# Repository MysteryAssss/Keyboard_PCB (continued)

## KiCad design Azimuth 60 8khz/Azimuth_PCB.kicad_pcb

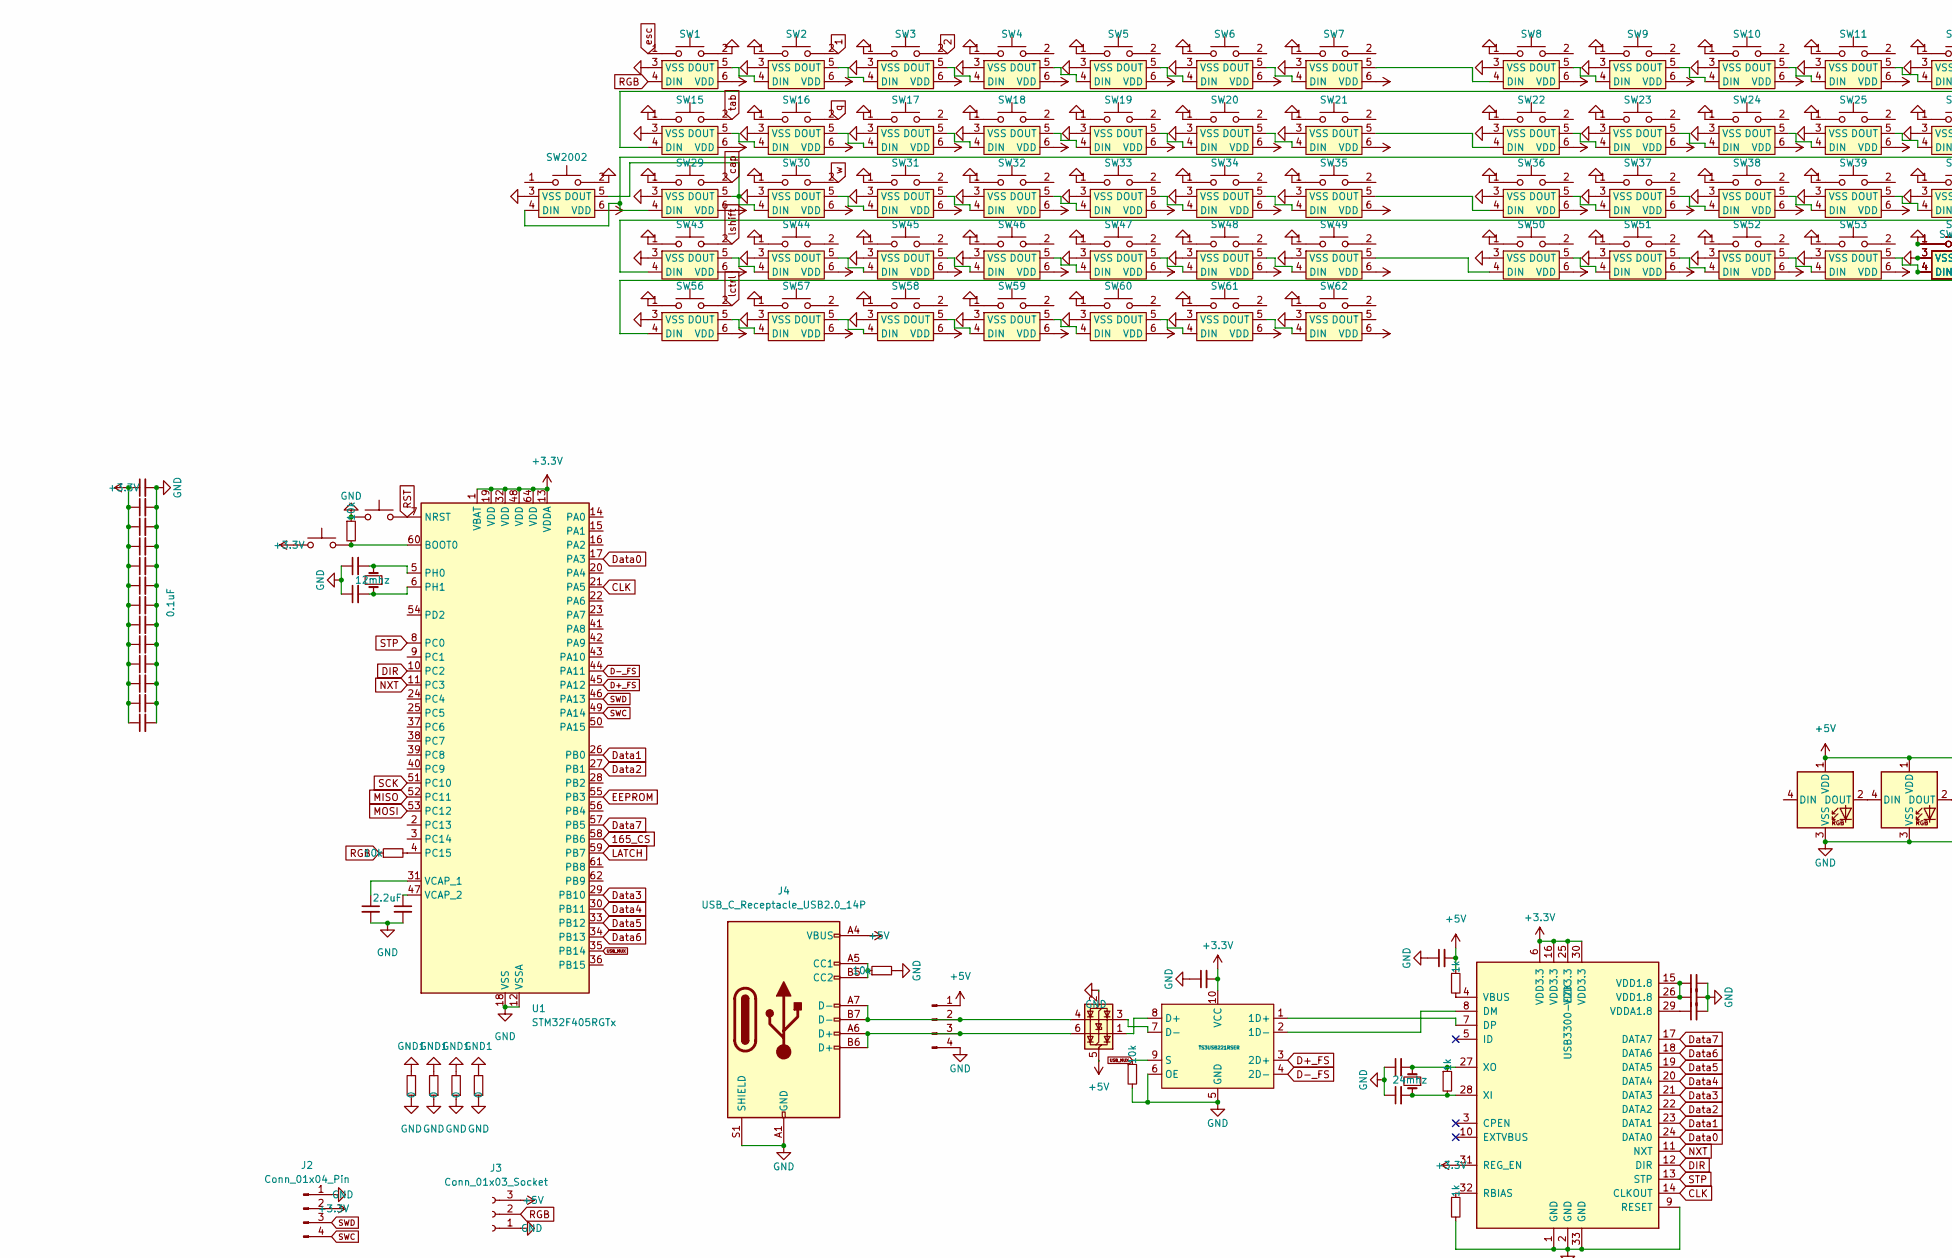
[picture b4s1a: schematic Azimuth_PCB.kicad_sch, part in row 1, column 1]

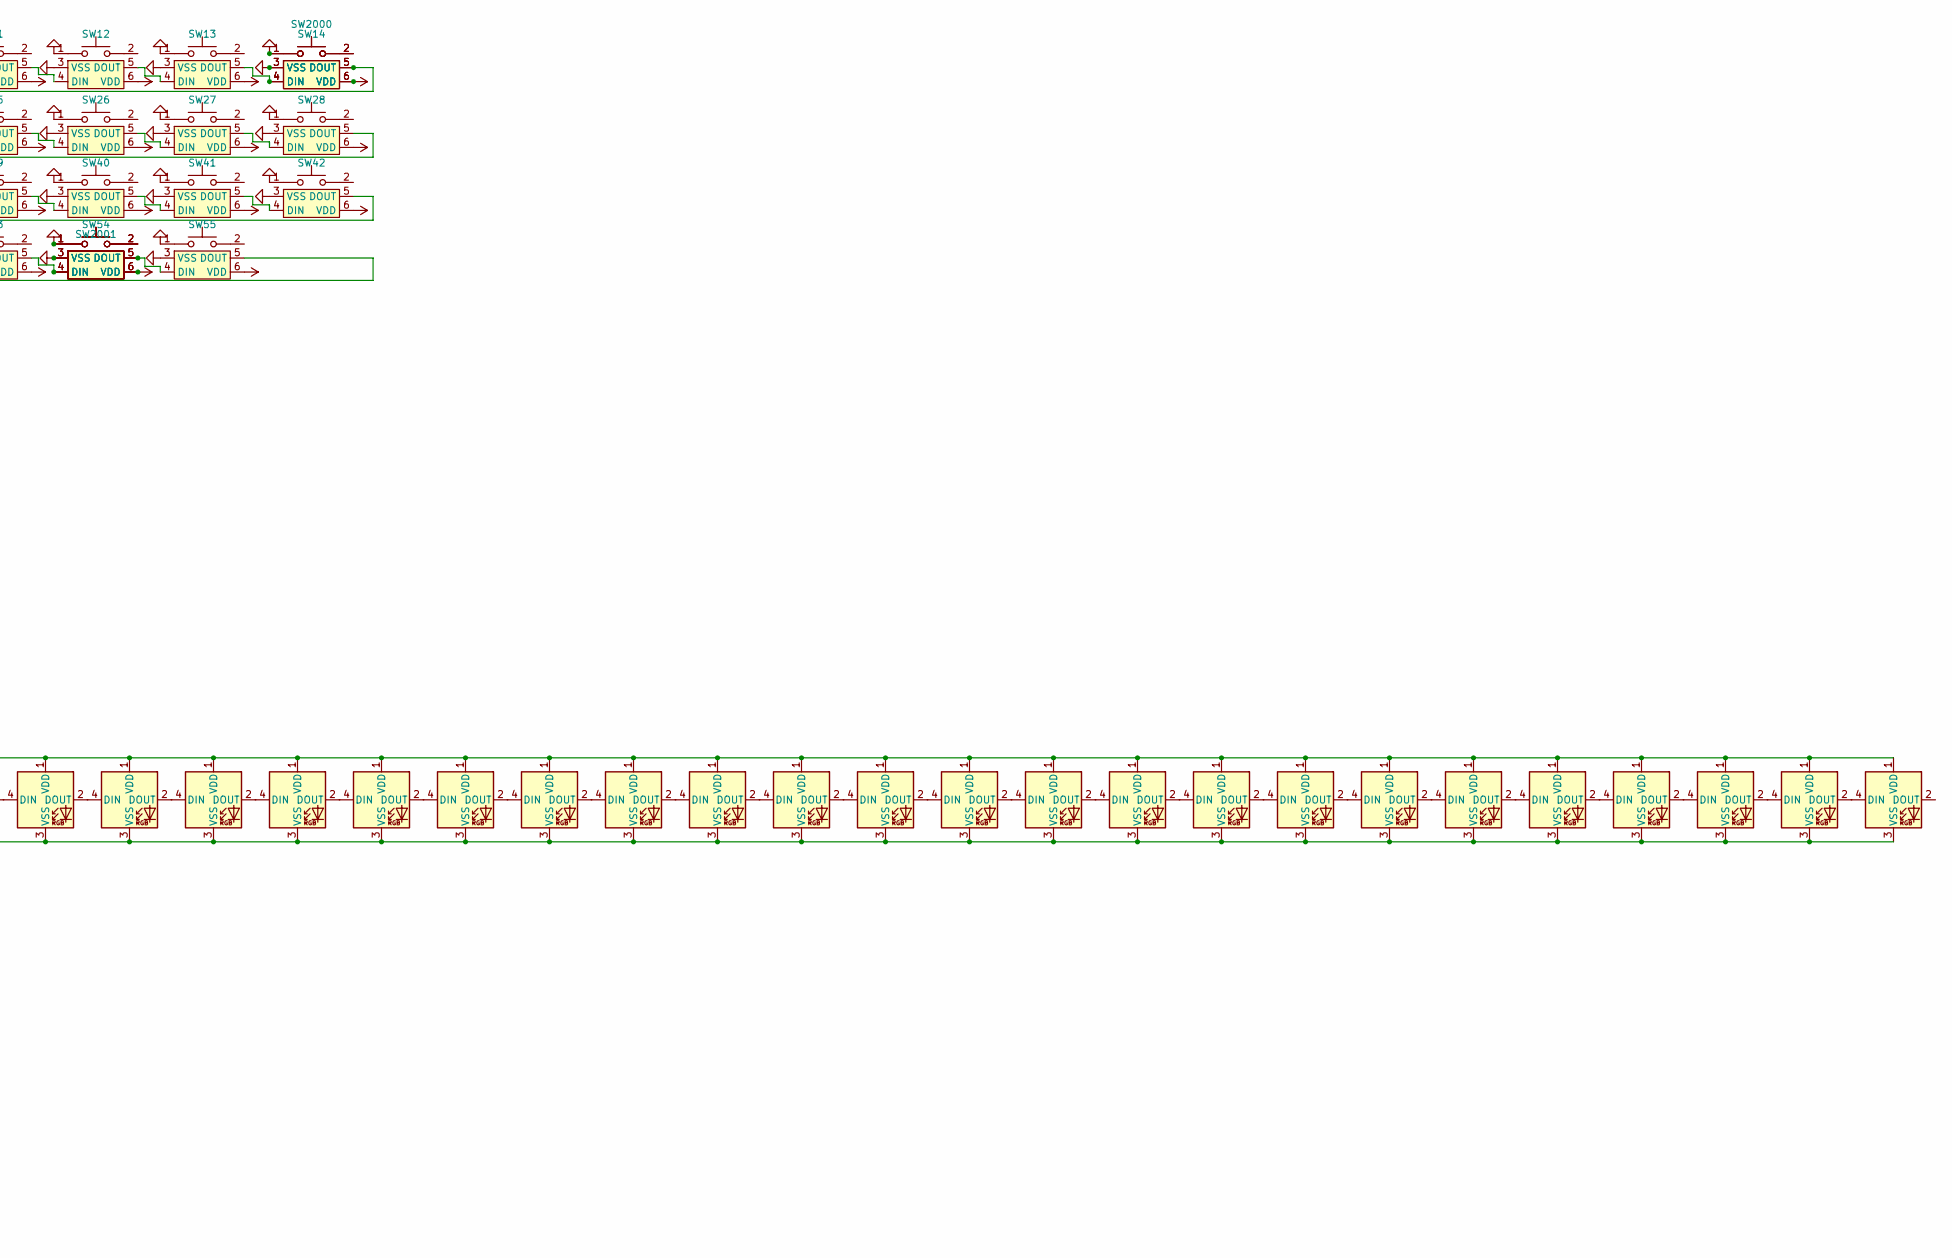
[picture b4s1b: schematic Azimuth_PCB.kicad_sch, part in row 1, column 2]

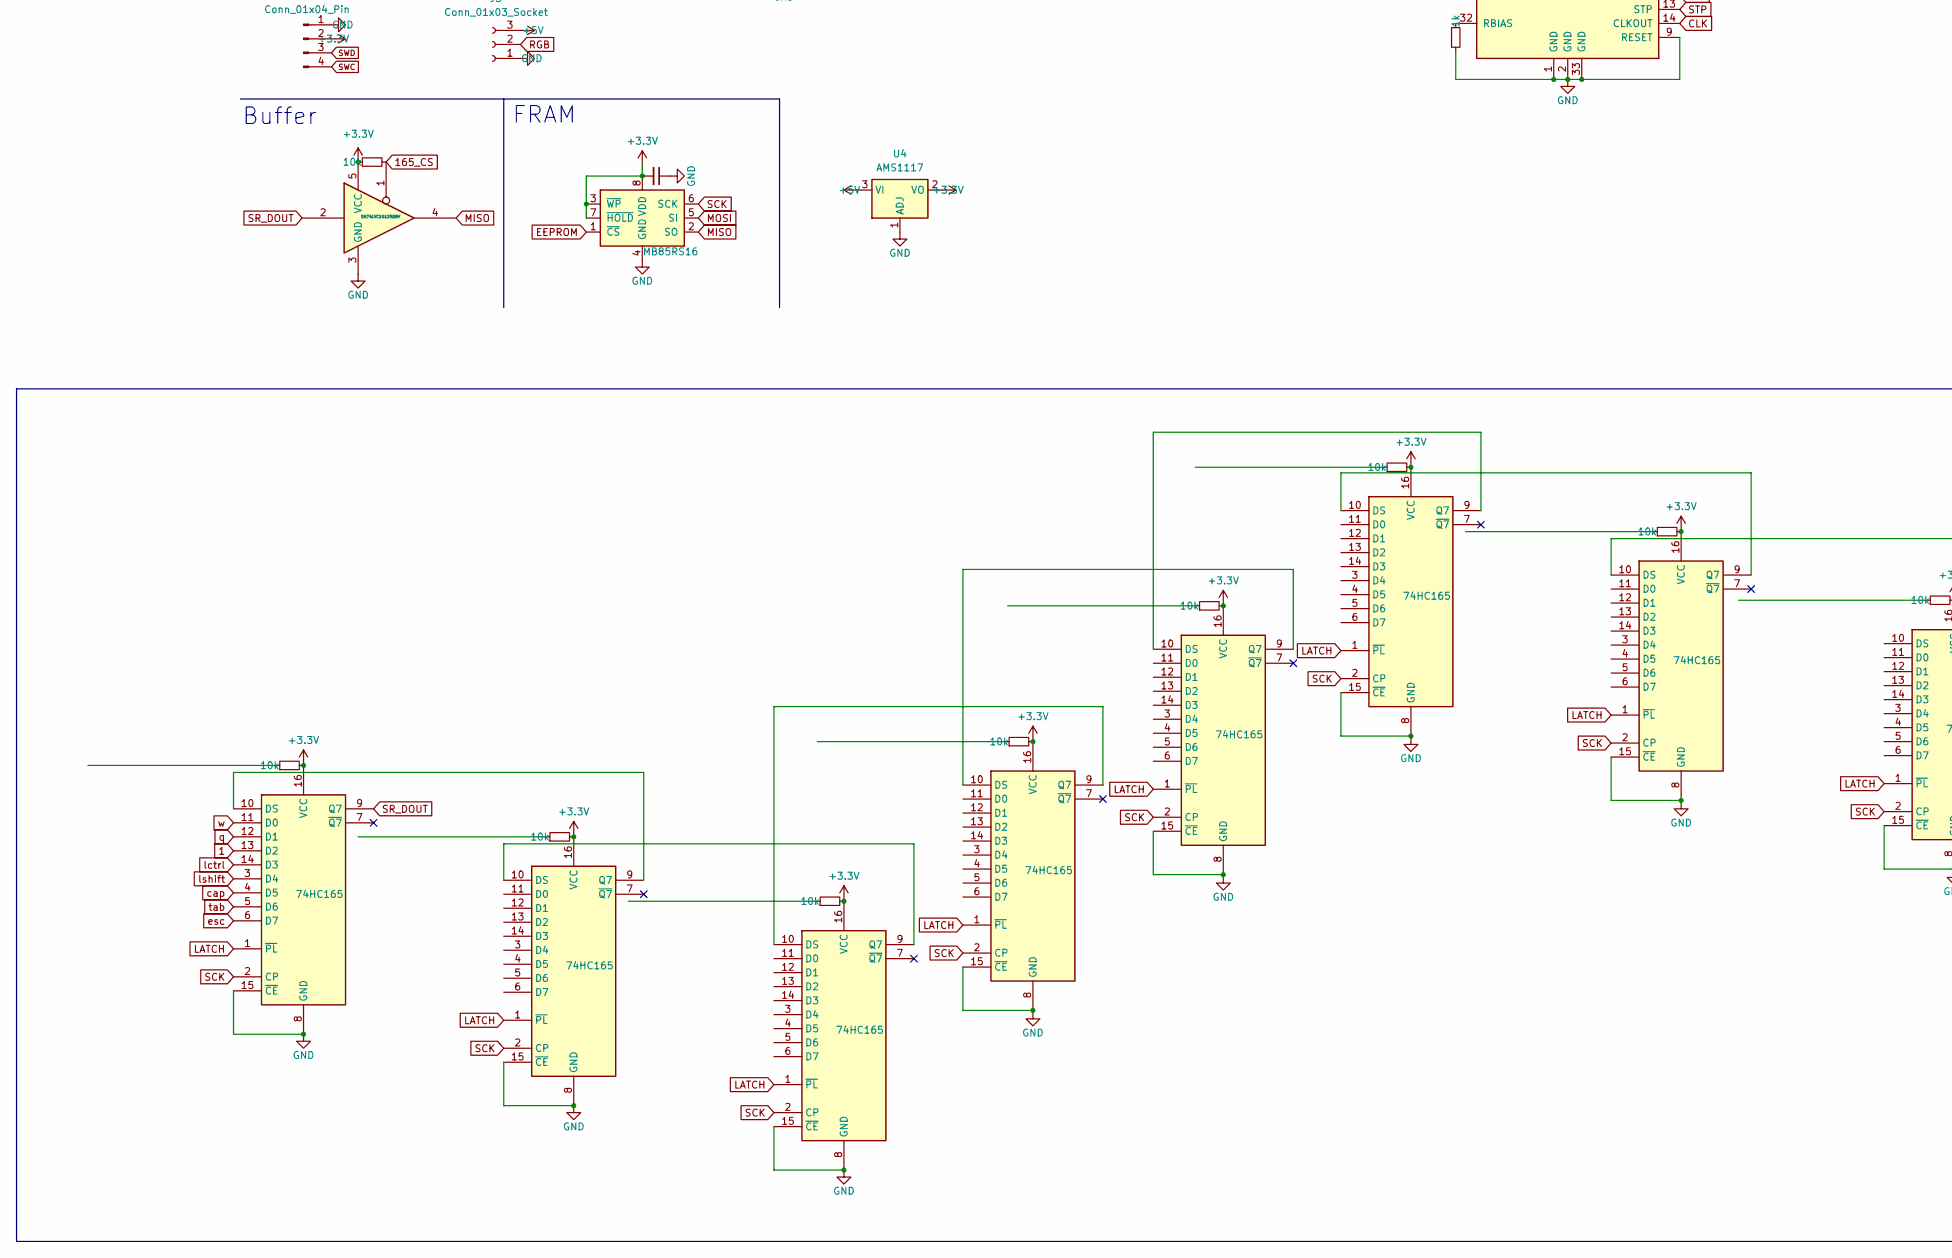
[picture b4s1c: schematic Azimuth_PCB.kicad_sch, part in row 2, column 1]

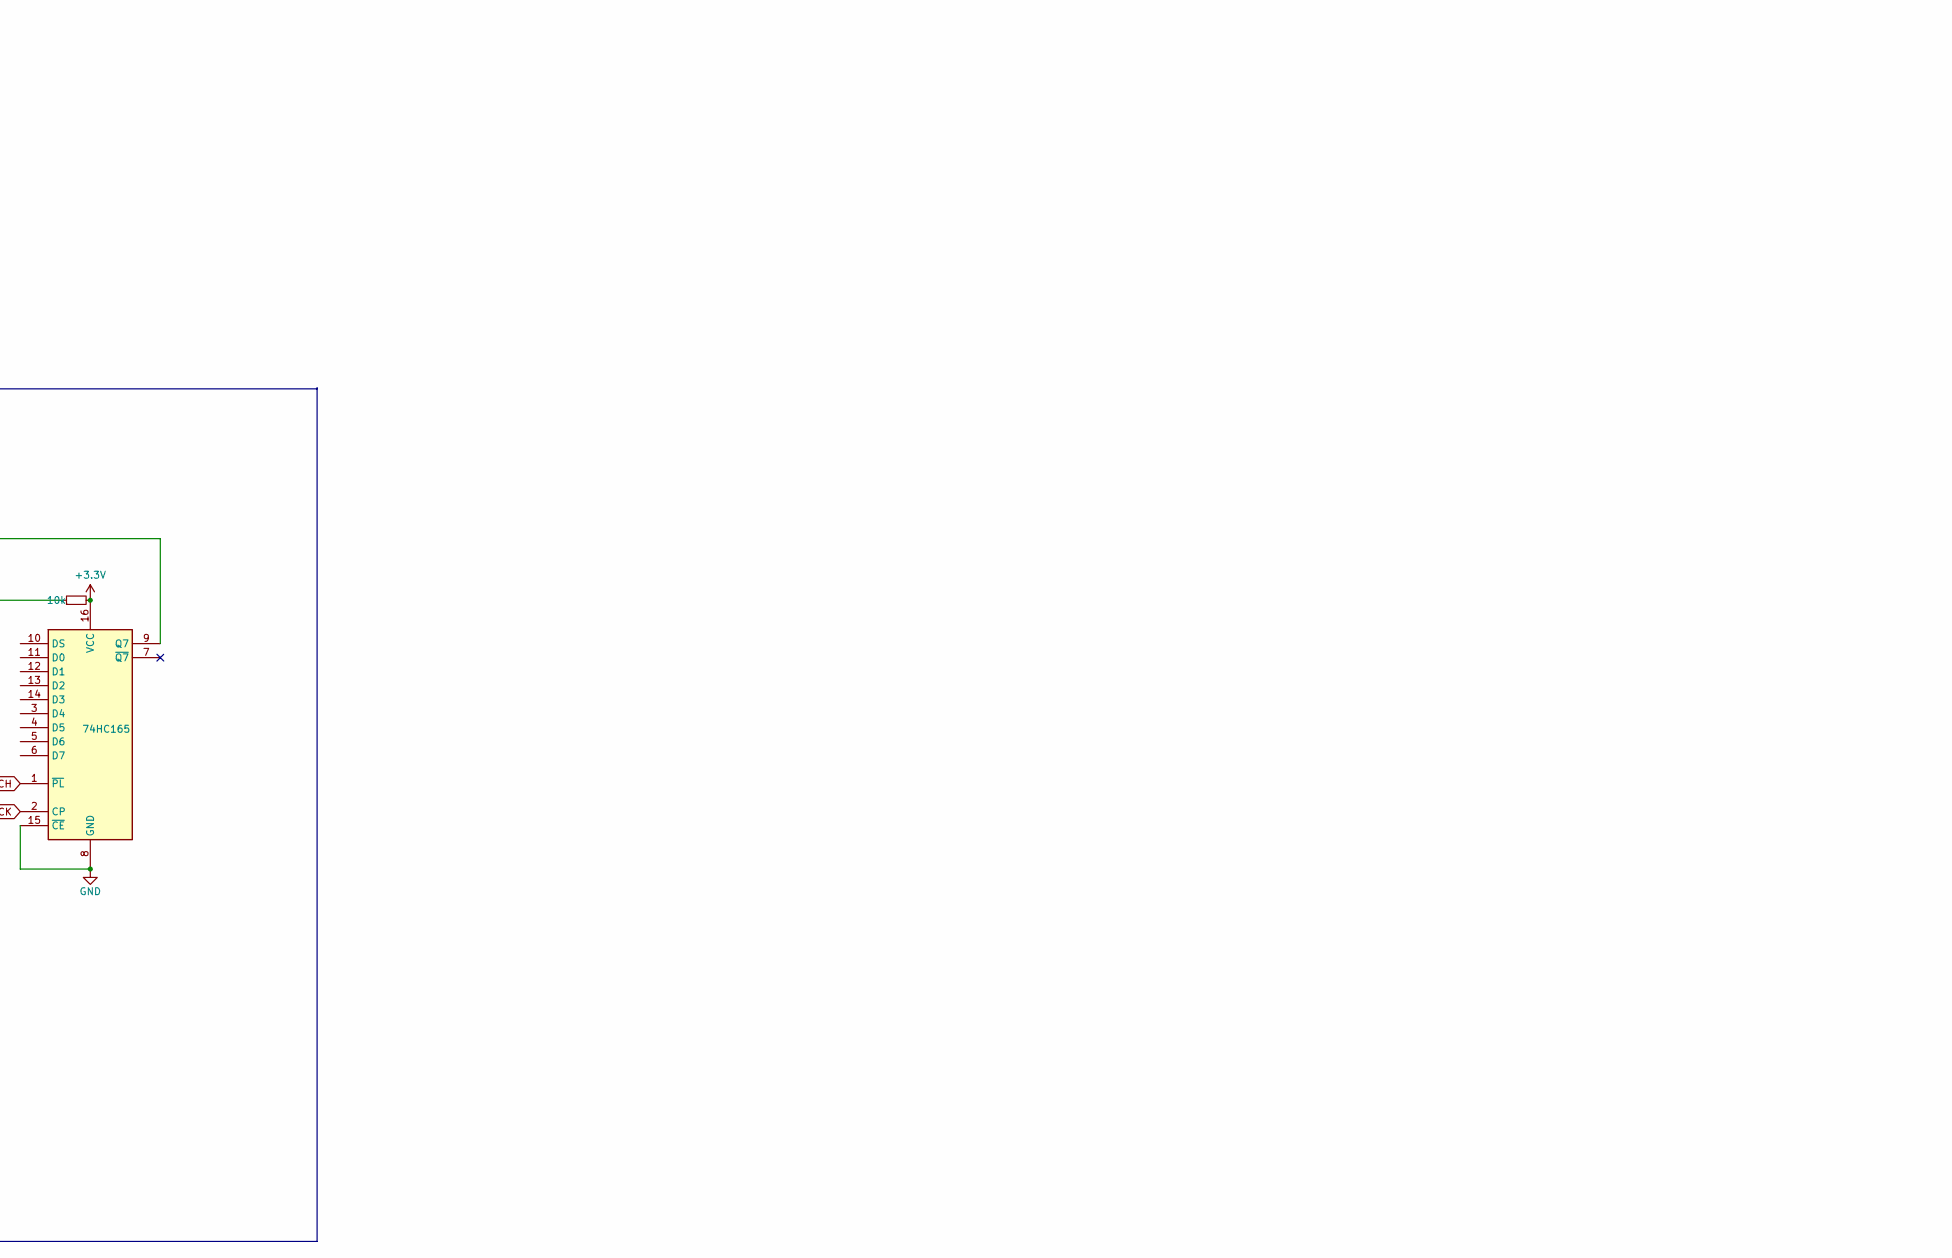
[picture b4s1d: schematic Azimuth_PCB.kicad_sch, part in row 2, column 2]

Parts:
C1, C2: 2.2uF; C_0603_1608Metric
C3, C4, C20, C21: 9pf; C_0603_1608Metric
C5, C6, C7, C8, C9, C10, C12, C14, C16: 0.1uF; C_0603_1608Metric
C11, C13, C15, C17, C18, C19, C22, C23, C24, C25: 1uF; C_0603_1608Metric
Drgb1, Drgb2, Drgb3, Drgb4, Drgb5, Drgb6, Drgb7, Drgb8, Drgb9, Drgb10, Drgb11, Drgb12, Drgb13, Drgb14, Drgb15, Drgb16, Drgb17, Drgb18, Drgb19, Drgb20, Drgb21, Drgb22, Drgb23, Drgb24: WS2812B; LED_WS2812B-2020_PLCC4_2.0x2.0mm
J1: Conn_01x04_Pin; JST_SH_SM04B-SRSS-TB_1x04-1MP_P1.00mm_Horizontal
J2: Conn_01x04_Pin; JST_EH_B4B-EH-A_1x04_P2.50mm_Vertical
J3: Conn_01x03_Socket; JST_SH_SM03B-SRSS-TB_1x03-1MP_P1.00mm_Horizontal
J4: USB_C_Receptacle_USB2.0_14P; USB_C_Receptacle_HRO_TYPE-C-31-M-12
R1, R2, R3, R4, R8, R9, R10, R11, R12, R13, R14, R15, R20: 10k; R_0603_1608Metric
R5, R6, R7: 1k; R_0603_1608Metric
R16, R17, R18, R19: 0; R_0603_1608Metric
SW1, SW2, SW3, SW4, SW5, SW6, SW7, SW8, SW9, SW10, SW11, SW12, SW13, SW14, SW16, SW17, SW18, SW19, SW20, SW21, SW22, SW23, SW24, SW25, SW26, SW27, SW30, SW31, SW32, SW33, SW34, SW35, SW36, SW37, SW38, SW39, SW40, SW42, SW44, SW45, SW46, SW47, SW48, SW49, SW50, SW51, SW52, SW53, SW55, SW57, SW61: CherryMX_LTST-A683CEGBW; MXOnly-1U_RGBs
SW15, SW28, SW56, SW58, SW60, SW62: CherryMX_LTST-A683CEGBW; MXOnly-1.5U_RGBs
SW29, SW54: CherryMX_LTST-A683CEGBW; MXOnly-1.75U_RGBs
SW41, SW43: CherryMX_LTST-A683CEGBW; MXOnly-2.25U_RGBs
SW59: CherryMX_LTST-A683CEGBW; MXOnly-7URGBs-ReversedStabilizers_N
SW2000: CherryMX_LTST-A683CEGBW; MXOnly-2U_RGBs
SW2001: CherryMX_LTST-A683CEGBW; MXOnly-2.75U_RGBs
SW2002: CherryMX_LTST-A683CEGBW; MXOnly-1.25U_RGBs
SWboot1, SWboot2: SW_Push; JST_XH_B2B-XH-A_1x02_P2.50mm_Vertical
U1: STM32F405RGTx; LQFP-64_10x10mm_P0.5mm
U2: SN74LVC1G125DBV; SOT-23-5
U3, U9, U10, U11, U12, U13, U14, U15: 74HC165; SOP-16_3.9x9.9mm_P1.27mm
U4: AMS1117; SOT-223-3_TabPin2
U5: TS3USB221RSER; UQFN-10
U6: USBLC6-2SC6; SOT-23-6
U7: USB3300-EZK; QFN-32-1EP_5x5mm_P0.5mm_EP3.45x3.45mm
U8: MB85RS16; SOIC-8_3.9x4.9mm_P1.27mm
Y1: 12mhz; Crystal_SMD_5032-2Pin_5.0x3.2mm
Y3: 24mhz; Crystal_SMD_5032-2Pin_5.0x3.2mm

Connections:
1: SW2.2, U3.13 (D2)
2: SW3.2
165_CS: R2.2, U1.58 (PB6), U2.1
+3.3V: C5.1, C6.1, C7.1, C8.1, C9.1, C10.1, C11.1, C12.1, C13.1, C14.1, C15.1, C16.1, C17.1, C18.2, C25.2, J2.2, R2.1, R3.2, R8.2, R9.2, R10.2, R11.2, R12.2, R13.2, R14.2, SWboot2.1, U1.1 (VBAT), U1.13 (VDDA), U1.19 (VDD), U1.32 (VDD), U1.48 (VDD), U1.64 (VDD), U2.5 (VCC), U3.16 (VCC), U4.2 (VO), U5.10 (VCC), U7.6 (VDD3.3), U7.16 (VDD3.3), U7.25 (VDD3.3), U7.30 (VDD3.3), U7.31 (REG_EN), U8.3 (~WP), U8.7 (~HOLD), U8.8 (VDD), U9.16 (VCC), U10.16 (VCC), U11.16 (VCC), U12.16 (VCC), U13.16 (VCC), U14.16 (VCC), U15.16 (VCC)
CLK: U1.21 (PA5), U7.14 (CLKOUT)
D+_FS: U1.45 (PA12), U5.3 (2D+)
D-_FS: U1.44 (PA11), U5.4 (2D-)
DIR: U1.10 (PC2), U7.12 (DIR)
Data0: U1.17 (PA3), U7.24 (DATA0)
Data1: U1.26 (PB0), U7.23 (DATA1)
Data2: U1.27 (PB1), U7.22 (DATA2)
Data3: U1.29 (PB10), U7.21 (DATA3)
Data4: U1.30 (PB11), U7.20 (DATA4)
Data5: U1.33 (PB12), U7.19 (DATA5)
Data6: U1.34 (PB13), U7.18 (DATA6)
Data7: U1.57 (PB5), U7.17 (DATA7)
EEPROM: U1.55 (PB3), U8.1 (~CS)
GND: C1.2, C2.2, C3.1, C4.1, C5.2, C6.2, C7.2, C8.2, C9.2, C10.2, C11.2, C12.2, C13.2, C14.2, C15.2, C16.2, C17.2, C18.1, C19.1, C20.1, C21.1, C22.2, C23.2, C24.2, C25.1, Drgb1.3 (VSS), Drgb2.3 (VSS), Drgb3.3 (VSS), Drgb4.3 (VSS), Drgb5.3 (VSS), Drgb6.3 (VSS), Drgb7.3 (VSS), Drgb8.3 (VSS), Drgb9.3 (VSS), Drgb10.3 (VSS), Drgb11.3 (VSS), Drgb12.3 (VSS), Drgb13.3 (VSS), Drgb14.3 (VSS), Drgb15.3 (VSS), Drgb16.3 (VSS), Drgb17.3 (VSS), Drgb18.3 (VSS), Drgb19.3 (VSS), Drgb20.3 (VSS), Drgb21.3 (VSS), Drgb22.3 (VSS), Drgb23.3 (VSS), Drgb24.3 (VSS), J1.4, J2.1, J3.1, J4.A1 (GND), J4.A12 (GND), J4.B1 (GND), J4.B12 (GND), J4.S1 (SHIELD), R1.1, R4.2, R7.2, R16.1, R17.1, R18.1, R19.1, R20.2, SW1.3 (VSS), SW2.3 (VSS), SW3.3 (VSS), SW4.3 (VSS), SW5.3 (VSS), SW6.3 (VSS), SW7.3 (VSS), SW8.3 (VSS), SW9.3 (VSS), SW10.3 (VSS), SW11.3 (VSS), SW12.3 (VSS), SW13.3 (VSS), SW14.3 (VSS), SW15.3 (VSS), SW16.3 (VSS), SW17.3 (VSS), SW18.3 (VSS), SW19.3 (VSS), SW20.3 (VSS), SW21.3 (VSS), SW22.3 (VSS), SW23.3 (VSS), SW24.3 (VSS), SW25.3 (VSS), SW26.3 (VSS), SW27.3 (VSS), SW28.3 (VSS), SW29.3 (VSS), SW30.3 (VSS), SW31.3 (VSS), SW32.3 (VSS), SW33.3 (VSS), SW34.3 (VSS), SW35.3 (VSS), SW36.3 (VSS), SW37.3 (VSS), SW38.3 (VSS), SW39.3 (VSS), SW40.3 (VSS), SW41.3 (VSS), SW42.3 (VSS), SW43.3 (VSS), SW44.3 (VSS), SW45.3 (VSS), SW46.3 (VSS), SW47.3 (VSS), SW48.3 (VSS), SW49.3 (VSS), SW50.3 (VSS), SW51.3 (VSS), SW52.3 (VSS), SW53.3 (VSS), SW54.3 (VSS), SW55.3 (VSS), SW56.3 (VSS), SW57.3 (VSS), SW58.3 (VSS), SW59.3 (VSS), SW60.3 (VSS), SW61.3 (VSS), SW62.3 (VSS), SW2000.3 (VSS), SW2001.3 (VSS), SW2002.3 (VSS), SWboot1.1, U1.12 (VSSA), U1.18 (VSS), U1.63 (VSS), U2.3 (GND), U3.8 (GND), U3.15 (~CE), U4.1 (ADJ), U5.5 (GND), U5.6 (OE), U6.2 (GND), U7.1 (GND), U7.2 (GND), U7.9 (RESET), U7.33 (GND), U8.4 (GND), U9.8 (GND), U9.15 (~CE), U10.8 (GND), U10.15 (~CE), U11.8 (GND), U11.15 (~CE), U12.8 (GND), U12.15 (~CE), U13.8 (GND), U13.15 (~CE), U14.8 (GND), U14.15 (~CE), U15.8 (GND), U15.15 (~CE)
GND1: R16.2, R17.2, R18.2, R19.2, SW1.2, SW2.1, SW3.1, SW4.1, SW5.1, SW6.1, SW7.1, SW8.1, SW9.1, SW10.1, SW11.1, SW12.1, SW13.1, SW14.1, SW15.1, SW16.1, SW17.1, SW18.1, SW19.1, SW20.1, SW21.1, SW22.1, SW23.1, SW24.1, SW25.1, SW26.1, SW27.1, SW28.1, SW29.1, SW30.1, SW31.1, SW32.1, SW33.1, SW34.1, SW35.1, SW36.1, SW37.1, SW38.1, SW39.1, SW40.1, SW41.1, SW42.1, SW43.1, SW44.1, SW45.1, SW46.1, SW47.1, SW48.1, SW49.1, SW50.1, SW51.1, SW52.1, SW53.1, SW54.1, SW55.1, SW56.1, SW57.1, SW58.1, SW59.1, SW60.1, SW61.1, SW62.1, SW2000.1, SW2001.1, SW2002.2
LATCH: U1.59 (PB7), U3.1 (~PL), U9.1 (~PL), U10.1 (~PL), U11.1 (~PL), U12.1 (~PL), U13.1 (~PL), U14.1 (~PL), U15.1 (~PL)
MISO: U1.52 (PC11), U2.4, U8.2 (SO)
MOSI: U1.53 (PC12), U8.5 (SI)
NXT: U1.11 (PC3), U7.11 (NXT)
unnamed: C22.1, C23.1, U7.15 (VDD1.8), U7.26 (VDD1.8)
unnamed: Drgb1.4 (DIN), Drgb16.2 (DOUT)
unnamed: Drgb1.2 (DOUT), Drgb2.4 (DIN)
unnamed: Drgb2.2 (DOUT), Drgb3.4 (DIN)
unnamed: Drgb3.2 (DOUT), Drgb4.4 (DIN)
unnamed: Drgb4.2 (DOUT), Drgb5.4 (DIN)
unnamed: Drgb5.2 (DOUT), Drgb6.4 (DIN)
unnamed: Drgb6.2 (DOUT), Drgb7.4 (DIN)
unnamed: Drgb7.2 (DOUT), Drgb8.4 (DIN)
unnamed: Drgb8.2 (DOUT), Drgb9.4 (DIN)
unnamed: Drgb9.2 (DOUT), Drgb10.4 (DIN)
unnamed: Drgb10.2 (DOUT), Drgb11.4 (DIN)
unnamed: Drgb11.2 (DOUT), Drgb12.4 (DIN)
unnamed: Drgb12.2 (DOUT), Drgb13.4 (DIN)
unnamed: Drgb13.2 (DOUT), Drgb14.4 (DIN)
unnamed: Drgb14.2 (DOUT), Drgb15.4 (DIN)
unnamed: Drgb15.2 (DOUT), Drgb17.4 (DIN)
unnamed: Drgb17.2 (DOUT), Drgb18.4 (DIN)
unnamed: Drgb18.2 (DOUT), Drgb19.4 (DIN)
unnamed: Drgb19.2 (DOUT), Drgb20.4 (DIN)
unnamed: Drgb20.2 (DOUT), Drgb21.4 (DIN)
unnamed: Drgb21.2 (DOUT), Drgb22.4 (DIN)
unnamed: Drgb22.2 (DOUT), Drgb23.4 (DIN)
unnamed: Drgb23.2 (DOUT), Drgb24.4 (DIN)
unnamed: J1.2, J4.A7 (D-), J4.B7 (D-), U6.4 (I/O2)
unnamed: J1.3, J4.A6 (D+), J4.B6 (D+), U6.6 (I/O1)
unnamed: J4.A5 (CC1), J4.B5 (CC2), R20.1
unnamed: SW1.5 (DOUT), SW2.4 (DIN)
unnamed: SW2.5 (DOUT), SW3.4 (DIN)
unnamed: SW3.5 (DOUT), SW4.4 (DIN)
unnamed: SW4.5 (DOUT), SW5.4 (DIN)
unnamed: SW5.5 (DOUT), SW6.4 (DIN)
unnamed: SW6.5 (DOUT), SW7.4 (DIN)
unnamed: SW7.5 (DOUT), SW8.4 (DIN)
unnamed: SW8.5 (DOUT), SW9.4 (DIN)
unnamed: SW9.5 (DOUT), SW10.4 (DIN)
unnamed: SW10.5 (DOUT), SW11.4 (DIN)
unnamed: SW11.5 (DOUT), SW12.4 (DIN)
unnamed: SW12.5 (DOUT), SW13.4 (DIN)
unnamed: SW13.5 (DOUT), SW14.4 (DIN), SW2000.4 (DIN)
unnamed: SW14.5 (DOUT), SW15.4 (DIN), SW2000.5 (DOUT)
unnamed: SW14.2, SW2000.2
unnamed: SW15.5 (DOUT), SW16.4 (DIN)
unnamed: SW16.5 (DOUT), SW17.4 (DIN)
unnamed: SW17.5 (DOUT), SW18.4 (DIN)
unnamed: SW18.5 (DOUT), SW19.4 (DIN)
unnamed: SW19.5 (DOUT), SW20.4 (DIN)
unnamed: SW20.5 (DOUT), SW21.4 (DIN)
unnamed: SW21.5 (DOUT), SW22.4 (DIN)
unnamed: SW22.5 (DOUT), SW23.4 (DIN)
unnamed: SW23.5 (DOUT), SW24.4 (DIN)
unnamed: SW24.5 (DOUT), SW25.4 (DIN)
unnamed: SW25.5 (DOUT), SW26.4 (DIN)
unnamed: SW26.5 (DOUT), SW27.4 (DIN)
unnamed: SW27.5 (DOUT), SW28.4 (DIN)
unnamed: SW30.5 (DOUT), SW31.4 (DIN)
unnamed: SW31.5 (DOUT), SW32.4 (DIN)
unnamed: SW32.5 (DOUT), SW33.4 (DIN)
unnamed: SW33.5 (DOUT), SW34.4 (DIN)
unnamed: SW34.5 (DOUT), SW35.4 (DIN)
unnamed: SW35.5 (DOUT), SW36.4 (DIN)
unnamed: SW36.5 (DOUT), SW37.4 (DIN)
unnamed: SW37.5 (DOUT), SW38.4 (DIN)
unnamed: SW38.5 (DOUT), SW39.4 (DIN)
unnamed: SW39.5 (DOUT), SW40.4 (DIN)
unnamed: SW40.5 (DOUT), SW41.4 (DIN)
unnamed: SW41.5 (DOUT), SW42.4 (DIN)
unnamed: SW42.5 (DOUT), SW43.4 (DIN)
unnamed: SW43.5 (DOUT), SW44.4 (DIN)
unnamed: SW44.5 (DOUT), SW45.4 (DIN)
unnamed: SW45.5 (DOUT), SW46.4 (DIN)
unnamed: SW46.5 (DOUT), SW47.4 (DIN)
unnamed: SW47.5 (DOUT), SW48.4 (DIN)
unnamed: SW48.5 (DOUT), SW49.4 (DIN)
unnamed: SW49.5 (DOUT), SW50.4 (DIN)
unnamed: SW50.5 (DOUT), SW51.4 (DIN)
unnamed: SW51.5 (DOUT), SW52.4 (DIN)
unnamed: SW52.5 (DOUT), SW53.4 (DIN)
unnamed: SW55.5 (DOUT), SW56.4 (DIN)
unnamed: SW56.5 (DOUT), SW57.4 (DIN)
unnamed: SW57.5 (DOUT), SW58.4 (DIN)
unnamed: SW58.5 (DOUT), SW59.4 (DIN)
unnamed: SW59.5 (DOUT), SW60.4 (DIN)
unnamed: SW60.5 (DOUT), SW61.4 (DIN)
unnamed: SW61.5 (DOUT), SW62.4 (DIN)
unnamed: SW53.5 (DOUT), SW54.4 (DIN), SW2001.4 (DIN)
unnamed: SW54.5 (DOUT), SW55.4 (DIN), SW2001.5 (DOUT)
unnamed: SW54.2, SW2001.2
unnamed: SW29.5 (DOUT), SW30.4 (DIN), SW2002.5 (DOUT)
unnamed: R1.2, SWboot2.2, U1.60 (BOOT0)
unnamed: R15.2, U1.4 (PC15)
unnamed: C3.2, U1.5 (PH0), Y1.2
unnamed: C4.2, U1.6 (PH1), Y1.1
unnamed: C2.1, U1.31 (VCAP_1)
unnamed: C1.1, U1.47 (VCAP_2)
unnamed: U3.10 (DS), U9.9 (Q7)
unnamed: U5.1 (1D+), U7.7 (DP)
unnamed: U5.2 (1D-), U7.8 (DM)
unnamed: U5.8 (D+), U6.1 (I/O1)
unnamed: U5.7 (D-), U6.3 (I/O2)
unnamed: R7.1, U7.32 (RBIAS)
unnamed: R5.2, U7.4 (VBUS)
unnamed: C24.1, U7.29 (VDDA1.8)
unnamed: C21.2, R6.2, U7.28 (XI), Y3.1
unnamed: C20.2, R6.1, U7.27 (XO), Y3.2
unnamed: U10.10 (DS), U11.9 (Q7)
unnamed: U9.10 (DS), U10.9 (Q7)
unnamed: U11.10 (DS), U12.9 (Q7)
unnamed: U12.10 (DS), U14.9 (Q7)
unnamed: U13.9 (Q7), U15.10 (DS)
unnamed: U14.10 (DS), U15.9 (Q7)
RGB: J3.2, R15.1, SW1.4 (DIN)
RST: SWboot1.2, U1.7 (NRST)
SCK: U1.51 (PC10), U3.2 (CP), U8.6 (SCK), U9.2 (CP), U10.2 (CP), U11.2 (CP), U12.2 (CP), U13.2 (CP), U14.2 (CP), U15.2 (CP)
SR_DOUT: U2.2, U3.9 (Q7)
STP: U1.8 (PC0), U7.13 (STP)
SWC: J2.4, U1.49 (PA14)
SWD: J2.3, U1.46 (PA13)
USB_MUX: R4.1, U1.35 (PB14), U5.9 (S)
cap: SW29.2, U3.4 (D5)
esc: SW1.1, U3.6 (D7)
lctrl: SW56.2, U3.14 (D3)
lshift: SW43.2, U3.3 (D4)
q: SW16.2, U3.12 (D1)
tab: SW15.2, U3.5 (D6)
w: SW30.2, U3.11 (D0)

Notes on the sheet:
FRAM
Buffer

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
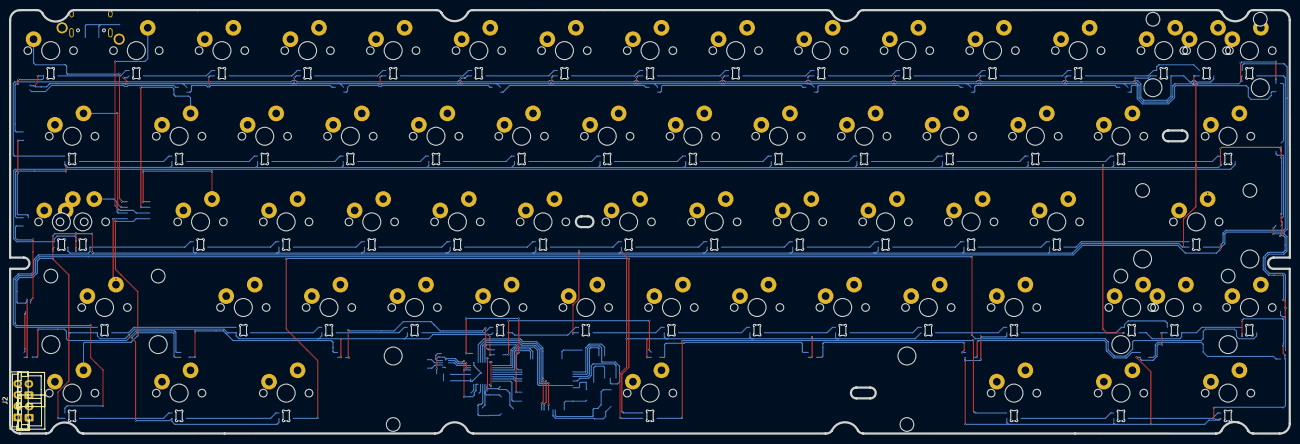
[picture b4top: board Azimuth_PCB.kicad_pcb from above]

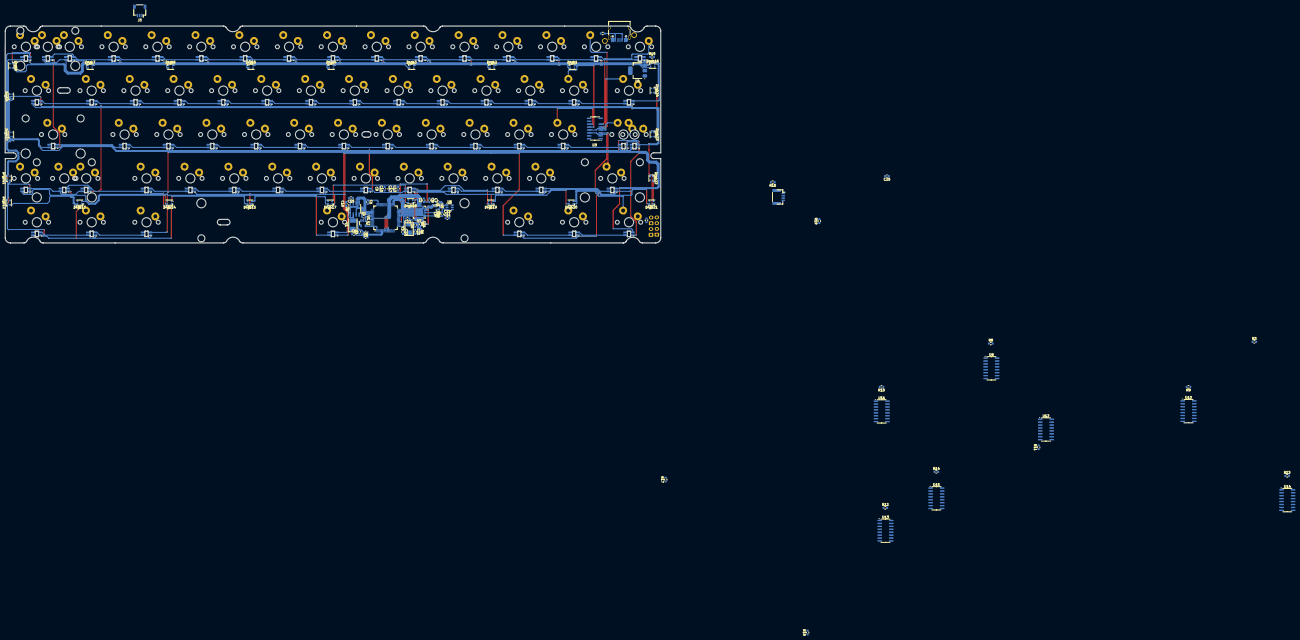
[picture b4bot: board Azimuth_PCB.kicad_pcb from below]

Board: 11 copper layers, 284.7 x 94.2 mm, 157 parts (89 on the bottom side), 150 nets.

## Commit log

2024-09-07 support for Unikorn, Tofu traymount, UTD365mini
